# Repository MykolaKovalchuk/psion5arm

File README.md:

# psion5arm
Psion Series 5 upgrade with ARM-based SBC

Used components:
- Non-working Psion Series 5 for parts;
- New Single Board Computer : Khadas Edge2;
- Screen: Khadas TS050 - 5" full HD (1920x1080) touchscreen;
- Khadas Edge2 IO board - for internal USB for keyboard, SD card reader, and amplifier with speakers contacts;
- Cirque GlidePoint Circle Trackpad, 23mm version - small trackpad;
- Raspberry Pi Pico - keyboard and trackpad controller;
- Small power bank with 12V 2A power delivery - tested with two different 5,000mAh 22.5W power banks (output 5V3A, 9V2.22A, 12V1.67A, 10V2.25A, 22.5W Max), works at least without heavy load;

Folder [KeyboardWithMouse](/KeyboardWithMouse/) contains:
- Firmware for Raspberry Pico Pi to control Psion keyboard and Cirque trackpad;
- KiCad files for PCB to connect Raspberry Pi with keyboard and trackpad via 22-pin and 12-pin flat cables.
Code files for keyboard and trackpad (identified as mouse) contain links to original code, libraries, and guaide, which I have used to prepare my version of this controller.

Internal components (during testing):

Components placement:

All components connected with lots of FPC flat cables and FPC extension boards (22pin for keyboard, 12pin for trackpad, 40pin for display+touchpad, 2 x 30pin for IO board).
Except Raspberry Pi connected to Khadas IO board via 4 wire USB interface (V, D+, D-, G).

Actual assembly:

3D models for new panels: https://www.printables.com/@MykolaKovalc_3575424/collections/2704362

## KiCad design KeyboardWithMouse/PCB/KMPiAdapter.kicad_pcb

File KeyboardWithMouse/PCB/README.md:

# KiCad scheme and pcb for a board to connect 22-pin FPC and 12-pin FPC to a Raspberry Pico.

Footprint for Raspberry Pico are from https://github.com/ncarandini/KiCad-RP-Pico

Footprints for 22-pin and 12-pin FPC connectors were imported from JLCPCB for available suitable parts.

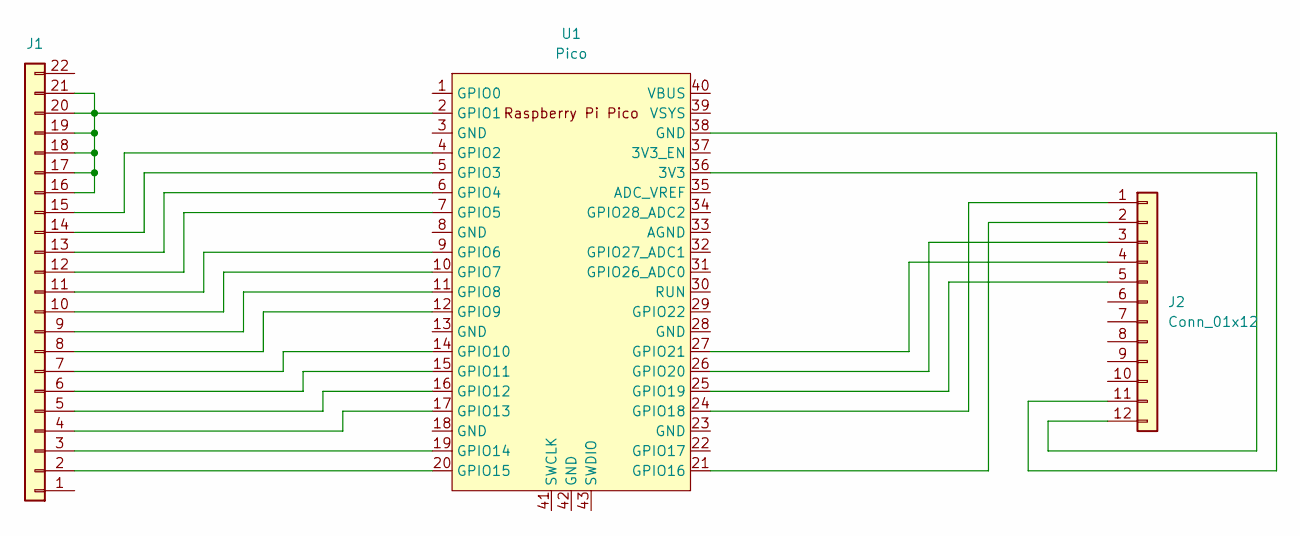
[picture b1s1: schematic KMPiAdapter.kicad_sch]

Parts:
J1: Conn_01x22; FPC-SMD_KH-FG0.5-H2.0-22PIN; LCSC Part # C2797212
J2: Conn_01x12; FPC-SMD_KH-FG0.5-H2.0-12PIN; LCSC Part # C709366
U1: Pico; RPi_Pico_SMD_TH

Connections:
unnamed: J1.2, U1.20 (GPIO15)
unnamed: J1.3, U1.19 (GPIO14)
unnamed: J1.4, U1.17 (GPIO13)
unnamed: J1.5, U1.16 (GPIO12)
unnamed: J1.6, U1.15 (GPIO11)
unnamed: J1.7, U1.14 (GPIO10)
unnamed: J1.8, U1.12 (GPIO9)
unnamed: J1.9, U1.11 (GPIO8)
unnamed: J1.10, U1.10 (GPIO7)
unnamed: J1.11, U1.9 (GPIO6)
unnamed: J1.12, U1.7 (GPIO5)
unnamed: J1.13, U1.6 (GPIO4)
unnamed: J1.14, U1.5 (GPIO3)
unnamed: J1.15, U1.4 (GPIO2)
unnamed: J1.16, J1.17, J1.18, J1.19, J1.20, J1.21, U1.2 (GPIO1)
unnamed: J2.1, U1.24 (GPIO18)
unnamed: J2.2, U1.21 (GPIO16)
unnamed: J2.3, U1.26 (GPIO20)
unnamed: J2.4, U1.27 (GPIO21)
unnamed: J2.5, U1.25 (GPIO19)
unnamed: J2.11, U1.38 (GND)
unnamed: J2.12, U1.36 (3V3)

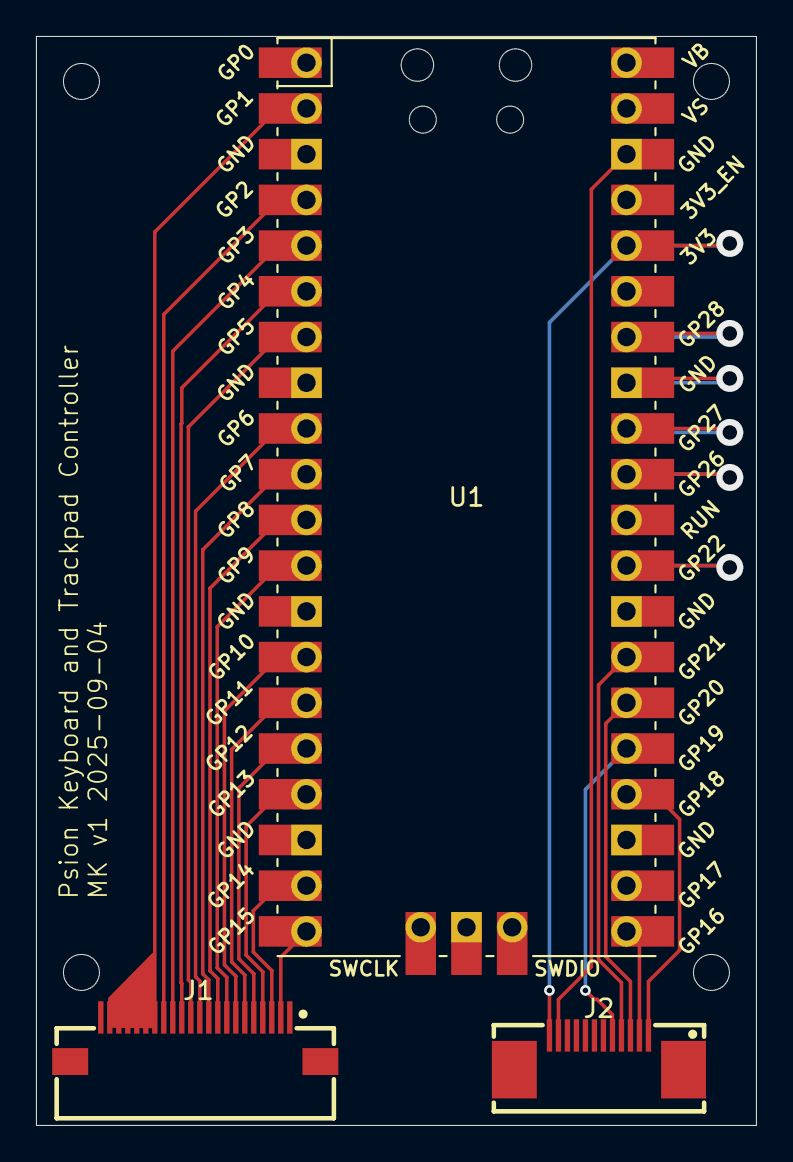
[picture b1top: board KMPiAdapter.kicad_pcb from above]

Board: 2 copper layers, 40.0 x 60.5 mm, 3 parts (0 on the bottom side), 22 nets.

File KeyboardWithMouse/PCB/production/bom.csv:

Designator,Footprint,Quantity,Value,LCSC Part #
J1,FPC-SMD_KH-FG0.5-H2.0-22PIN,1,Conn_01x22,C2797212
J2,FPC-SMD_KH-FG0.5-H2.0-12PIN,1,Conn_01x12,C709366

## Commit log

2025-04-22 Initial RPi Pico project
2025-04-29 USB Keyboard for Pico in Arduino
2025-04-30 Clean keyboard driver files
2025-04-30 Fn keymap and caps lock
2025-04-30 Full Fn key support
2025-04-30 Added F1-F10 support (Fn + F + 1..0 = F1..F10)
2025-05-01 Use GPIO 1-15 - all on one side of RP2040 chip
2025-05-06 Delete .vscode/c_cpp_properties.json
    Keyboard driver was done in Arduino IDE, and VS Code settings for it are not needed.
2025-07-21 Initial virtual mouse implementation. Plus experiment with trackpad.
2025-07-29 Cirque Glidepoint trackpad support
2025-07-30 Combined keyboard and trackpad driver
2025-09-06 Use custom LED instead built in
2025-10-04 Control volume with brightness buttons
2025-10-04 PCB KiCad file with compiled production gerber files
2025-10-04 Readme files
2025-10-04 Fix images
2025-10-04 Move test drivers to Testing folder
2025-10-04 Components and assembly
2025-10-04 Link to 3D models for new panels
2025-10-04 Improved readme
2025-10-04 Link fix
2025-10-24 Internal components photo
